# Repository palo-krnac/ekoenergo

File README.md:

# ekoenergo – Solar Water Heating Inverter

**ekoenergo** is an open source project of a solar inverter for heating domestic hot water. It can be used to power a boiler coil and connect electric resistance heating coils and radiators.

This inverter is specifically designed to optimize the use of photovoltaic (PV) panels for powering a standard electric heating element in a domestic hot water (DHW) storage tank (boiler). It converts direct current (DC) from PV panels into alternating current (AC) with a 50 Hz rectangular waveform and a variable duty cycle ranging from approximately **3% to 98%**.

In automatic mode, the inverter continuously measures **voltage and current** to calculate the output power of the PV panels. It dynamically adjusts the duty cycle to maintain the **Maximum Power Point Tracking (MPPT)**, ensuring optimal energy extraction.

Without this feature, a fixed full-duty load on the panels — especially in **low-light conditions** — would cause voltage to drop, resulting in minimal power output. Thanks to MPPT, the inverter excels even in weak or fluctuating sunlight, such as during **early mornings, evenings, cloudy skies, or partial shading**.

> **Example:**  
> If the duty cycle is manually set to 100% under weak sunlight, you might get only **300 W** from a nominal **750 W** PV system. With MPPT, the inverter adjusts the load to extract significantly more energy.

---

## Installation and Usage Guidelines

- Place the inverter as **close to the boiler** as possible.
- Connect **only resistive loads** to the output terminals (e.g., heating element, immersion heater, standard boiler **without** electronics or contactors).
- Do **not** connect the output to:
  - Ground
  - Other inverters
  - External voltage sources

---

## Technical Specifications

| Parameter                            | Value                                |
|--------------------------------------|--------------------------------------|
| **Max PV input voltage (open circuit)** | 400 V DC                            |
| **Continuous output current**         | 8–9 A                                |
| **Maximum output current**            | 10 A                                 |
| **Maximum output power**              | approx. 2800 W                       |
| **Recommended PV array**             | 8 panels, 260–280 Wp each            |
| **Recommended heating element**      | 2–3 kW / 230 V                       |
| **Minimum resistive load**           | approx. 15 Ω                         |

---

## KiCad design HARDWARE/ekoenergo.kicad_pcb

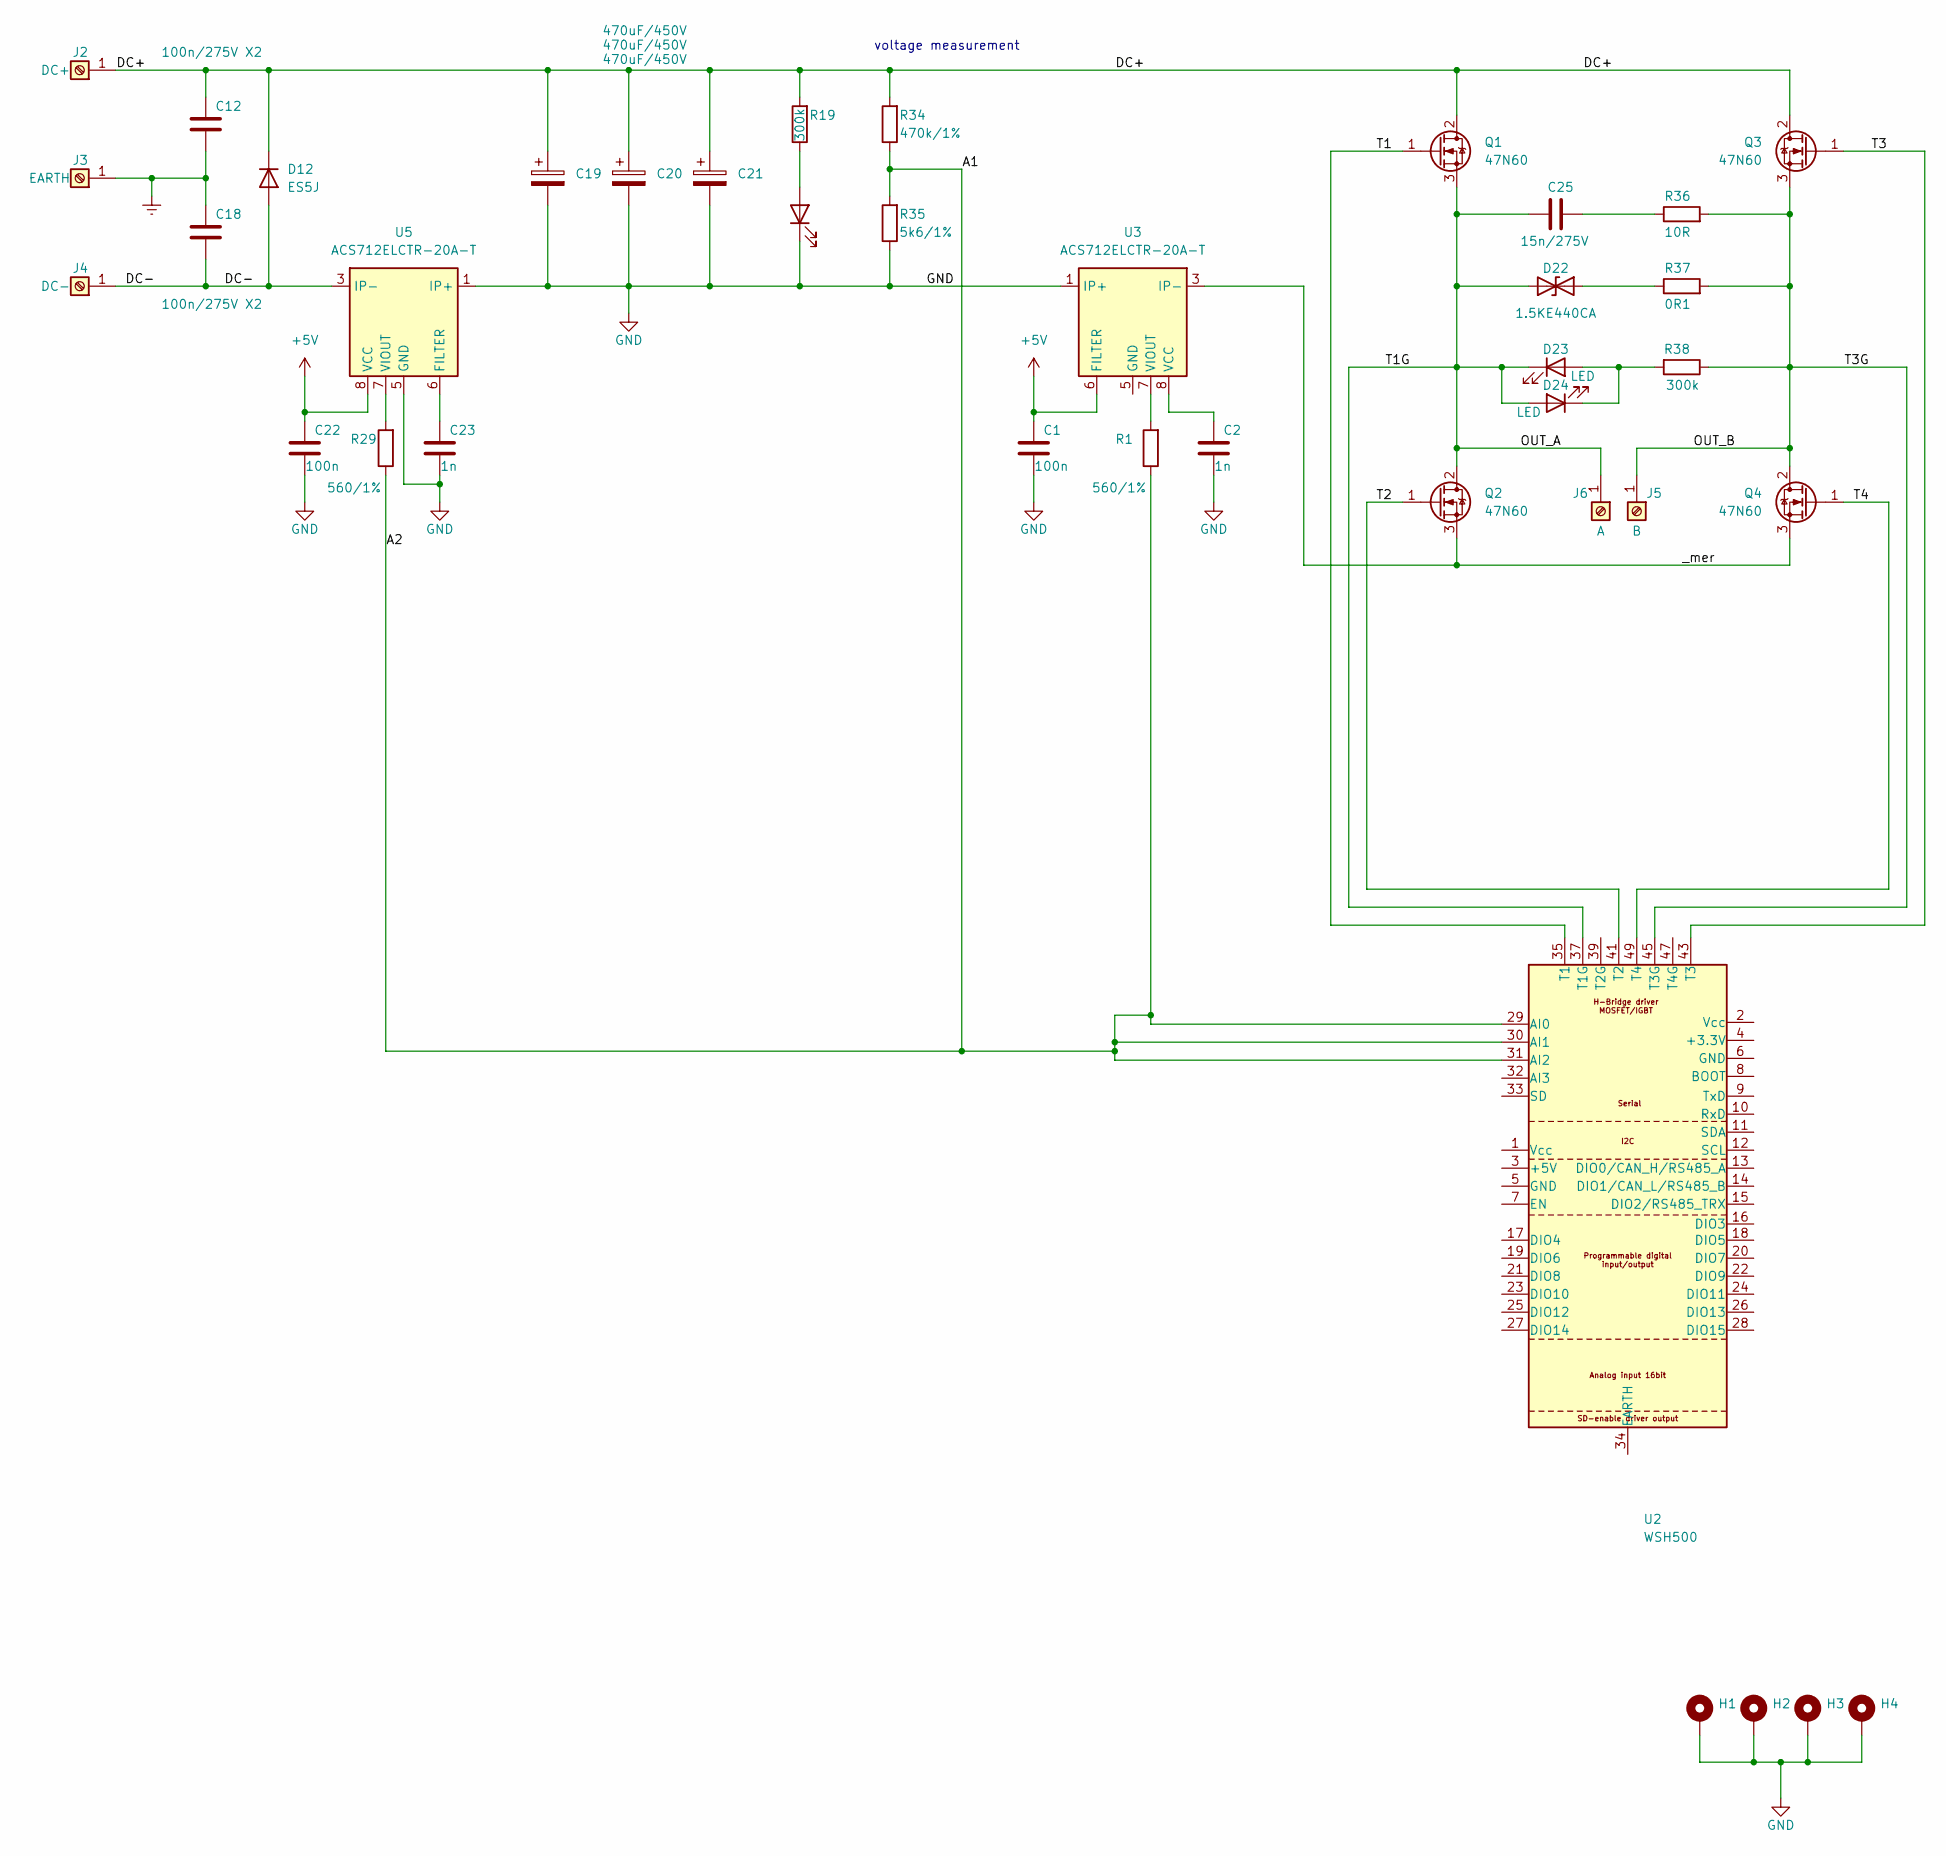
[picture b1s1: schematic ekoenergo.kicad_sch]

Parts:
C1, C22: 100n; C_0805_2012Metric
C2, C23: 1n; C_0805_2012Metric
C12, C18: 100n/275V X2; C_Rect_L13.0mm_W8.0mm_P10.00mm_FKS3_FKP3_MKS4
C19, C20, C21: 470uF/450V; WE_861011486024
C25: 15n/275V
D12: ES5J; D_SMB
D17, D23, D24: LED; LED_0805_2012Metric
D22: 1.5KE440CA; D_DO-201AE_P15.24mm_Horizontal
H1, H2, H3, H4: 3,2; MountingHole_3.2mm_M3_Pad_Via
J2: DC+; KEYS_7796
J3: EARTH; KEYS_7796
J4: DC-; KEYS_7796
J5: B; KEYS_7796
J6: A; KEYS_7796
Q1, Q2, Q3, Q4: 47N60; TO-247-3_Horizontal_TabDown_Cut
R1, R29: 560/1%; R_0805_2012Metric
R19, R38: 300k; R_0805_2012Metric
R34: 470k/1%; R_0805_2012Metric
R35: 5k6/1%; R_0805_2012Metric
R36: 10R
R37: 0R1
U2: WSH500; WSH500_SMD
U3, U5: ACS712ELCTR-20A-T; SOIC-8_3.9x4.9mm_P1.27mm

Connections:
+5V: C1.1, C22.1, U3.6 (FILTER), U5.8 (VCC)
/A1: R1.1, R29.1, R34.1, R35.2, U2.29 (AI0), U2.30 (AI1), U2.31 (AI2)
/DC+: C12.1, C19.1, C20.1, C21.1, D12.1, J2.1, Q1.2 (D), Q3.2 (D), R19.2, R34.2
/DC-: C18.2, D12.2, J4.1, U5.3 (IP-), U5.4 (IP-)
/OUT_A: C25.1, D22.1 (A1), D23.1 (K), D24.2 (A), J6.1, Q1.3 (S), Q2.2 (D), U2.37 (T1G), U2.38 (T1G)
/OUT_B: J5.1, Q3.3 (S), Q4.2 (D), R36.2, R37.2, R38.1, U2.45 (T3G), U2.46 (T3G)
/T1: Q1.1 (G), U2.35 (T1), U2.36 (T1)
/T2: Q2.1 (G), U2.41 (T2), U2.42 (T2)
/T3: Q3.1 (G), U2.43 (T3), U2.44 (T3)
/T4: Q4.1 (G), U2.49 (T4), U2.50 (T4)
/_mer: Q2.3 (S), Q4.3 (S), U3.3 (IP-), U3.4 (IP-)
Earth: C12.2, C18.1, J3.1
GND: C1.2, C2.2, C19.2, C20.2, C21.2, C22.2, C23.2, D17.1 (K), H1.1, H2.1, H3.1, H4.1, R35.1, U3.1 (IP+), U3.2 (IP+), U5.1 (IP+), U5.2 (IP+), U5.5 (GND)
unnamed: C25.2, R36.1
unnamed: D17.2 (A), R19.1
unnamed: D22.2 (A2), R37.1
unnamed: D23.2 (A), D24.1 (K), R38.2
unnamed: U2.39 (T2G), U2.40 (T2G)
unnamed: U2.47 (T4G), U2.48 (T4G)
unnamed: C2.1, U3.8 (VCC)
unnamed: R1.2, U3.7 (VIOUT)
unnamed: C23.1, U5.6 (FILTER)
unnamed: R29.2, U5.7 (VIOUT)

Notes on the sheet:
voltage measurement

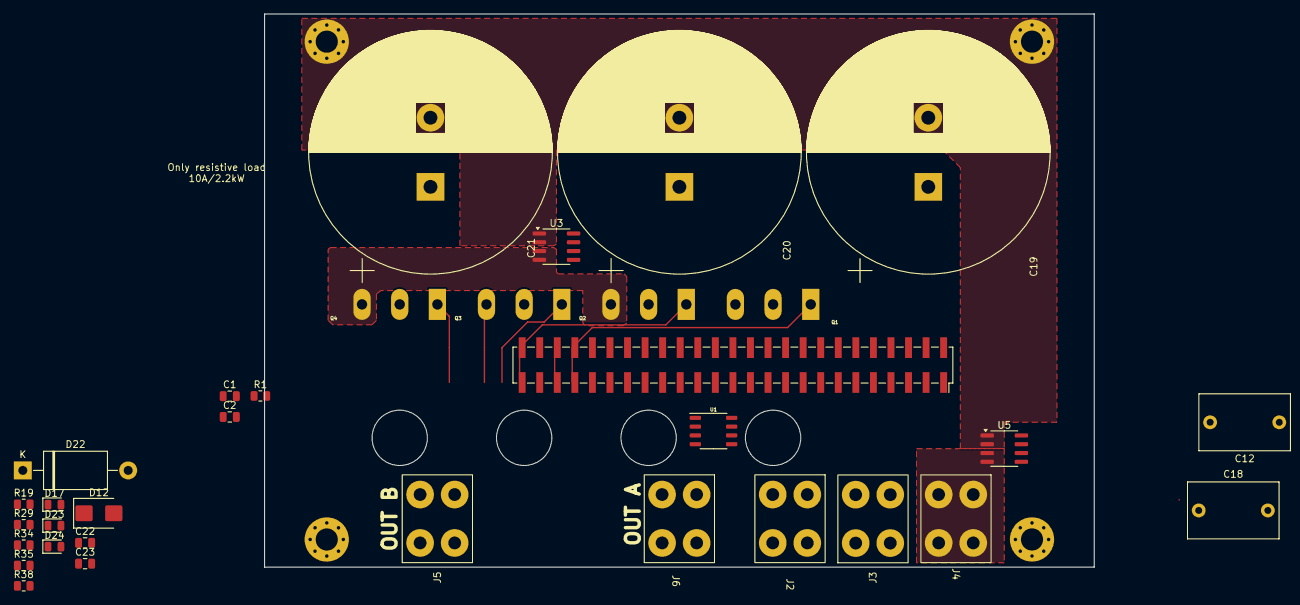
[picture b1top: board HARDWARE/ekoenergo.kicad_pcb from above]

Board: 4 copper layers, 120.0 x 80.0 mm, 37 parts (0 on the bottom side), 21 nets.

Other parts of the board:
U1: WS3081; SOP-8_3.9x4.9mm_P1.27mm

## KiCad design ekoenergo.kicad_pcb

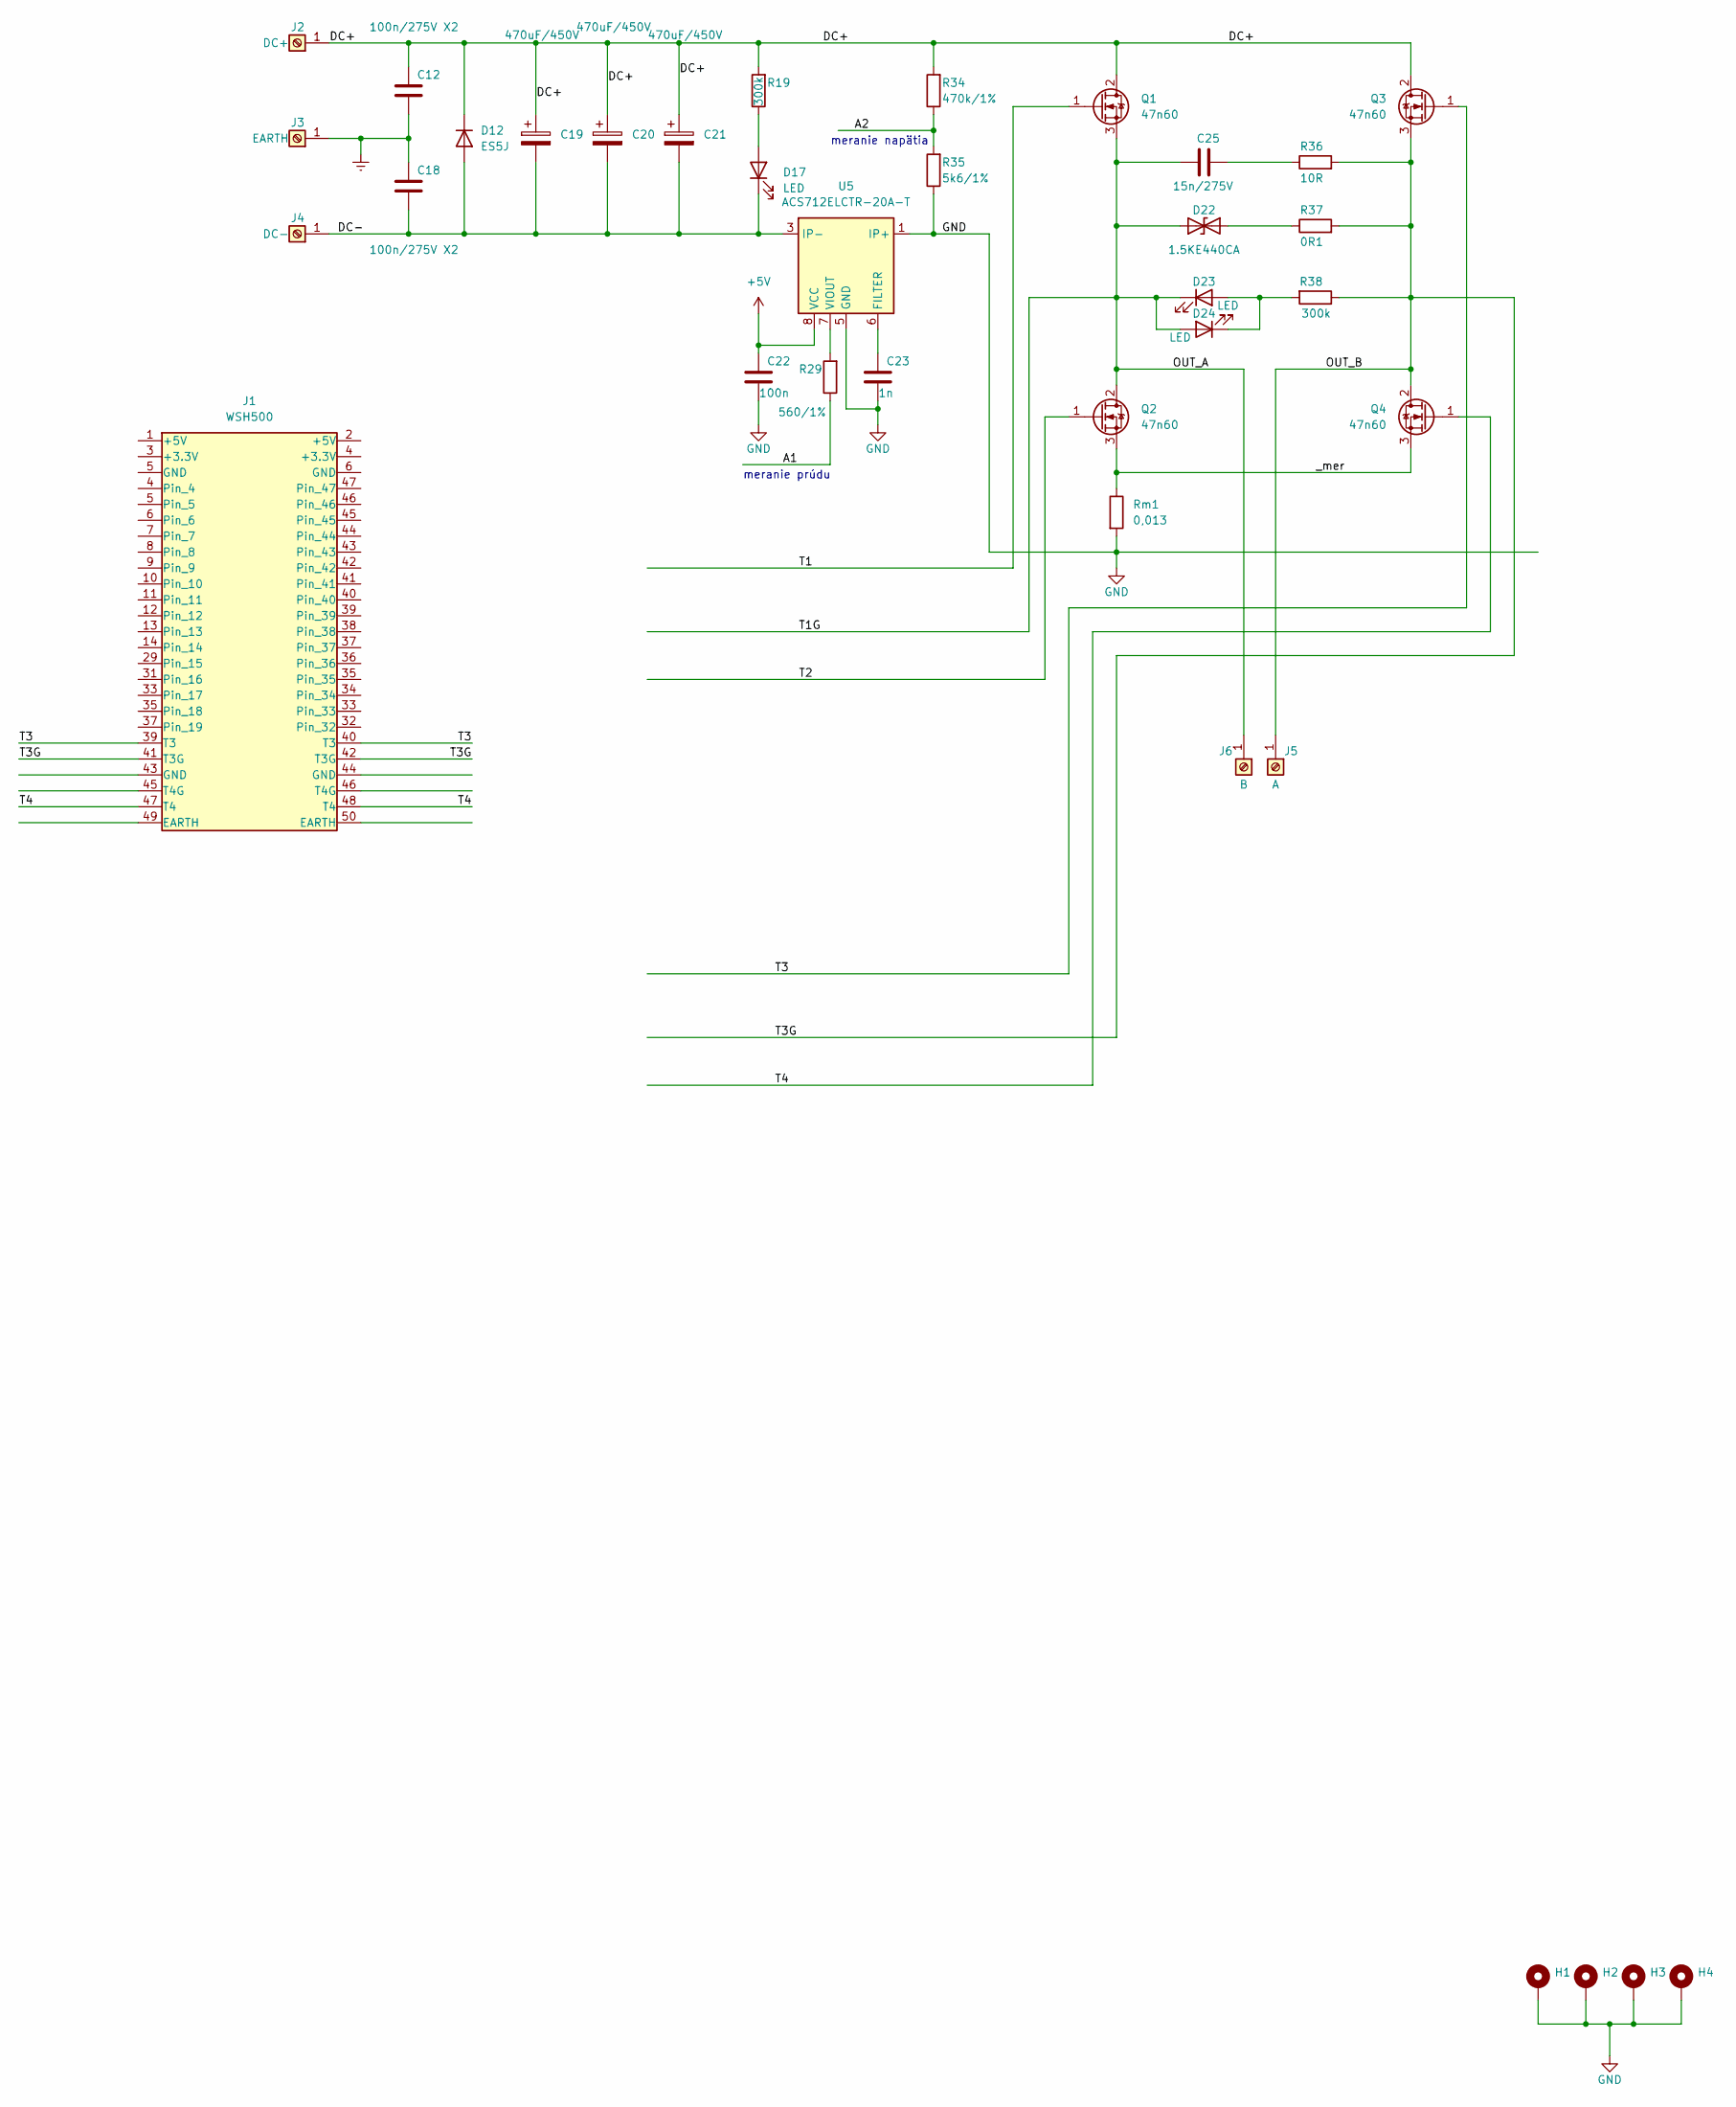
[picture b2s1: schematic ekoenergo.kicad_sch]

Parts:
C12, C18: 100n/275V X2; C_Rect_L13.0mm_W8.0mm_P10.00mm_FKS3_FKP3_MKS4
C19, C20, C21: 470uF/450V; WE_861011486024
C22: 100n; C_0805_2012Metric
C23: 1n; C_0805_2012Metric
C25: 15n/275V
D12: ES5J; D_SMB
D17, D23, D24: LED; LED_0805_2012Metric
D22: 1.5KE440CA; D_DO-201AE_P15.24mm_Horizontal
H1, H2, H3, H4: 3,2; MountingHole_3.2mm_M3_Pad_Via
J1: WSH500
J2: DC+; KEYS_7796
J3: EARTH; KEYS_7796
J4: DC-; KEYS_7796
J5: A; KEYS_7796
J6: B; KEYS_7796
Q1, Q2, Q3, Q4: 47n60; TO-247-3_Horizontal_TabDown_Cut
R19, R38: 300k; R_0805_2012Metric
R29: 560/1%; R_0805_2012Metric
R34: 470k/1%; R_0805_2012Metric
R35: 5k6/1%; R_0805_2012Metric
R36: 10R
R37: 0R1
Rm1: 0,013; R_2816_7142Metric
U5: ACS712ELCTR-20A-T; SOIC-8_3.9x4.9mm_P1.27mm

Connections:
+5V: C22.1, U5.8 (VCC)
/A1: R29.1
/A2: R34.1, R35.2
/DC+: C12.1, C19.1, C20.1, C21.1, D12.1, J2.1, Q1.2 (D), Q3.2 (D), R19.2, R34.2
/DC-: C18.2, C19.2, C20.2, C21.2, D12.2, D17.1 (K), J4.1, U5.3 (IP-), U5.4 (IP-)
/OUT_A: C25.1, D22.1 (A1), D23.1 (K), D24.2 (A), J6.1, Q1.3 (S), Q2.2 (D)
/OUT_B: J1.41 (T3G), J1.42 (T3G), J5.1, Q3.3 (S), Q4.2 (D), R36.2, R37.2, R38.1
/T1: Q1.1 (G)
/T2: Q2.1 (G)
/T3: J1.39 (T3), J1.40 (T3), Q3.1 (G)
/T4: J1.47 (T4), J1.48 (T4), Q4.1 (G)
/_mer: Q2.3 (S), Q4.3 (S), Rm1.1
Earth: C12.2, C18.1, J3.1
GND: C22.2, C23.2, H1.1, H2.1, H3.1, H4.1, R35.1, Rm1.2, U5.1 (IP+), U5.2 (IP+), U5.5 (GND)
unnamed: C25.2, R36.1
unnamed: D17.2 (A), R19.1
unnamed: D22.2 (A2), R37.1
unnamed: D23.2 (A), D24.1 (K), R38.2
unnamed: C23.1, U5.6 (FILTER)
unnamed: R29.2, U5.7 (VIOUT)

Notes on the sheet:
meranie napätia
meranie prúdu

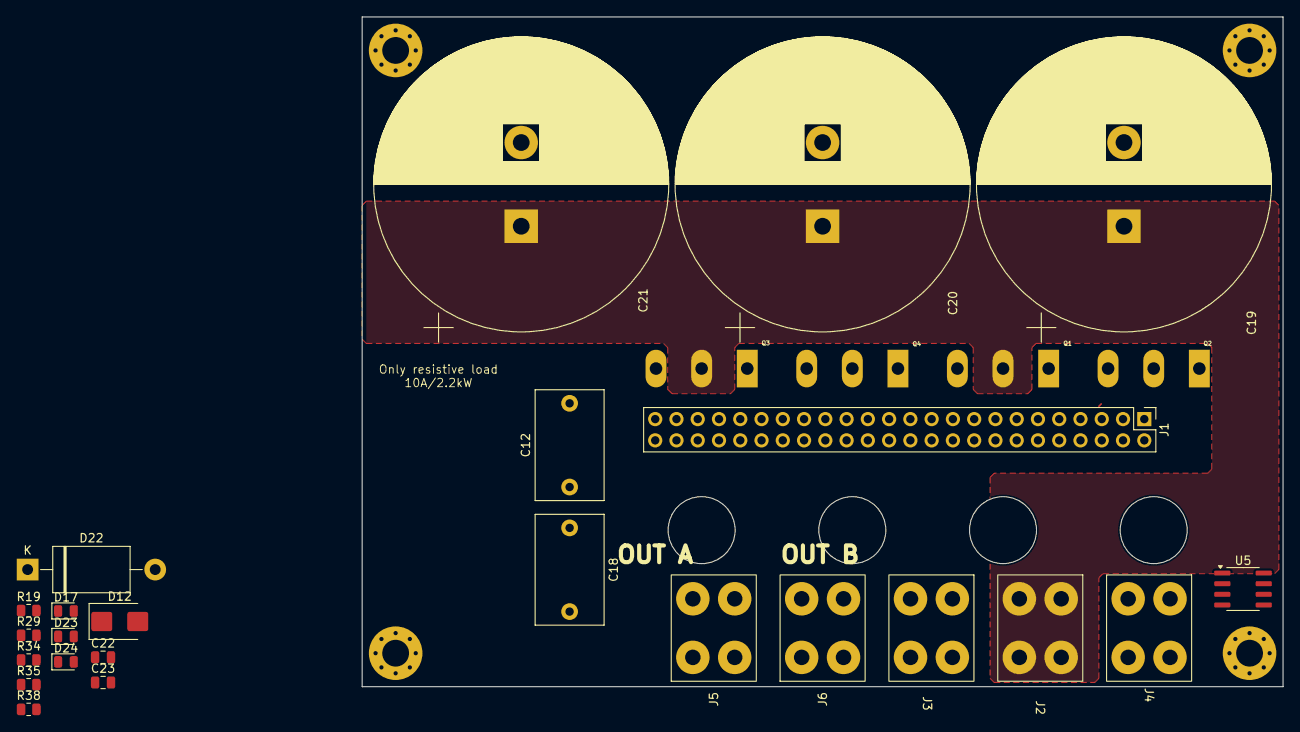
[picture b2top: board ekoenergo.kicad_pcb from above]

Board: 4 copper layers, 110.0 x 80.0 mm, 33 parts (1 on the bottom side), 15 nets.

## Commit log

2025-05-17 create repository ekoenergo
2025-05-17 update_schematics
2025-05-17 upload_files
